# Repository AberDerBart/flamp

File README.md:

**Disclaimer:** This has been developed as a personal project and the current state was good enough for me to build it but is problably not well suited to recreate.
There are also changes planned (especially to the PCB and electronics).
Please contact me or open an issue if you have any problems or questions on this project, I am happy to help (but not very motivated to do documentation work upfront).

If you want or need another license for some reason (especially for commercial use), feel free to contact me.

# Flamp

These are the design files for my flower lamp (short "Flamp"), A dimmable ceiling lamp inspired by a flower blossom with servo-actuated petals to open up or close down.

## Getting started

Check out this repository using the [`--recurse-submodules`](https://git-scm.com/docs/git-clone#Documentation/git-clone.txt---recurse-submodulespathspec) flag.

For the mechanical design, open `lamp.scad` in OpenSCAD. This gives an overview how the lamp is assembled.

For the PCB design, open [pcb/pcb.kicad_pro](pcb/pcb.kicad_pro) in KiCad.

## Necessary parts

For hardware and electronic parts, see [BOM.csv](BOM.csv).
You need to 3D print the parts from [cad/printed_parts.scad](cad/printed_parts.scad).
The design for the wooden parts can be found in [cad/wooden_parts_12mm.scad](cad/wooden_parts_12mm.scad) and [cad/wooden_parts_4mm.scad](cad/wooden_parts_4mm.scad).

1. Cut the parts with a CNC router or laser cutter from 12mm or 4mm plywood respectively
2. 3D print the [jigs](cad/jigs.scad) and use them to trace the shape of the wooden parts and saw them out.
   Then, use the jigs and a router to trim them to size and drill the holes using the jigs. Make sure to drill the holes before removing the inner parts.

## Assembly

TODO

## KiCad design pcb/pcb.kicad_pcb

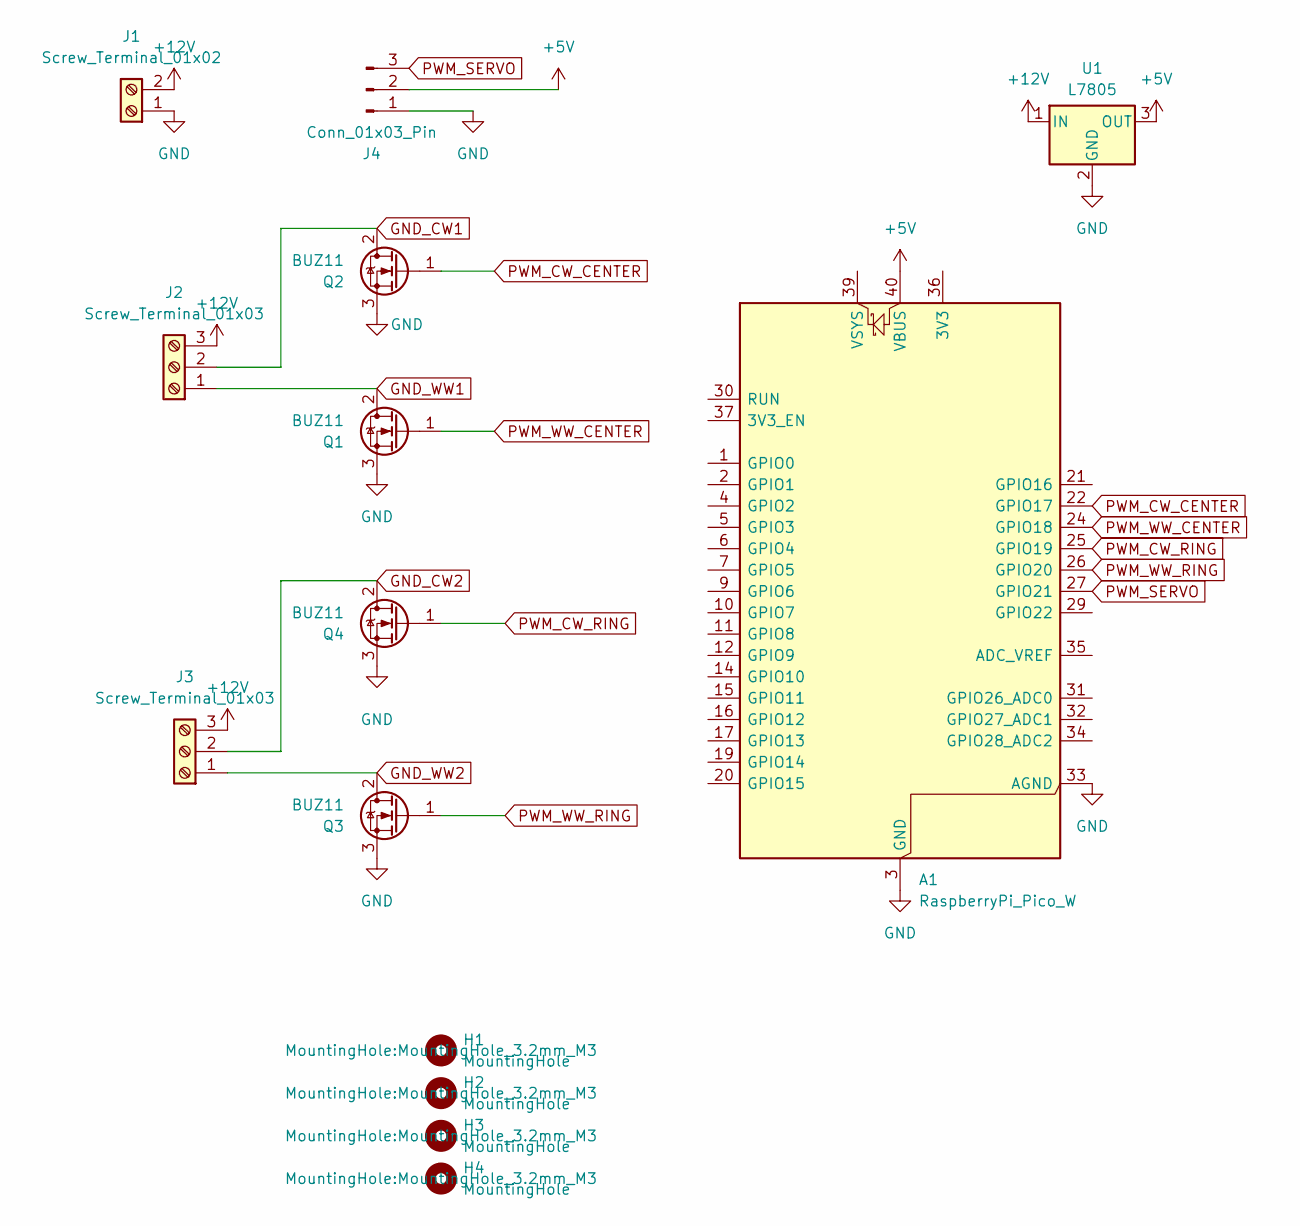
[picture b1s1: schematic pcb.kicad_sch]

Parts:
A1: RaspberryPi_Pico_W; RaspberryPi_Pico_Common_THT
H1, H2, H3, H4: MountingHole; MountingHole_3.2mm_M3
J1: Screw_Terminal_01x02; TerminalBlock_Phoenix_PT-1,5-2-3.5-H_1x02_P3.50mm_Horizontal
J2, J3: Screw_Terminal_01x03; TerminalBlock_Phoenix_PT-1,5-3-3.5-H_1x03_P3.50mm_Horizontal
J4: Conn_01x03_Pin; PinHeader_1x03_P2.54mm_Vertical
Q1, Q2, Q3, Q4: BUZ11; TO-220-3_Horizontal_TabDown
U1: L7805; TO-220-3_Horizontal_TabUp

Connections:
+5V: A1.40 (VBUS), J4.2, U1.3 (OUT)
+12V: J1.2, J2.3, J3.3, U1.1 (IN)
GND: A1.3 (GND), A1.8 (GND), A1.13 (GND), A1.18 (GND), A1.23 (GND), A1.28 (GND), A1.33 (AGND), A1.38 (GND), J1.1, J4.1, Q1.3 (S), Q2.3 (S), Q3.3 (S), Q4.3 (S), U1.2 (GND)
GND_CW1: J2.2, Q2.2 (D)
GND_CW2: J3.2, Q4.2 (D)
GND_WW1: J2.1, Q1.2 (D)
GND_WW2: J3.1, Q3.2 (D)
PWM_CW_CENTER: A1.22 (GPIO17), Q2.1 (G)
PWM_CW_RING: A1.25 (GPIO19), Q4.1 (G)
PWM_SERVO: A1.27 (GPIO21), J4.3
PWM_WW_CENTER: A1.24 (GPIO18), Q1.1 (G)
PWM_WW_RING: A1.26 (GPIO20), Q3.1 (G)

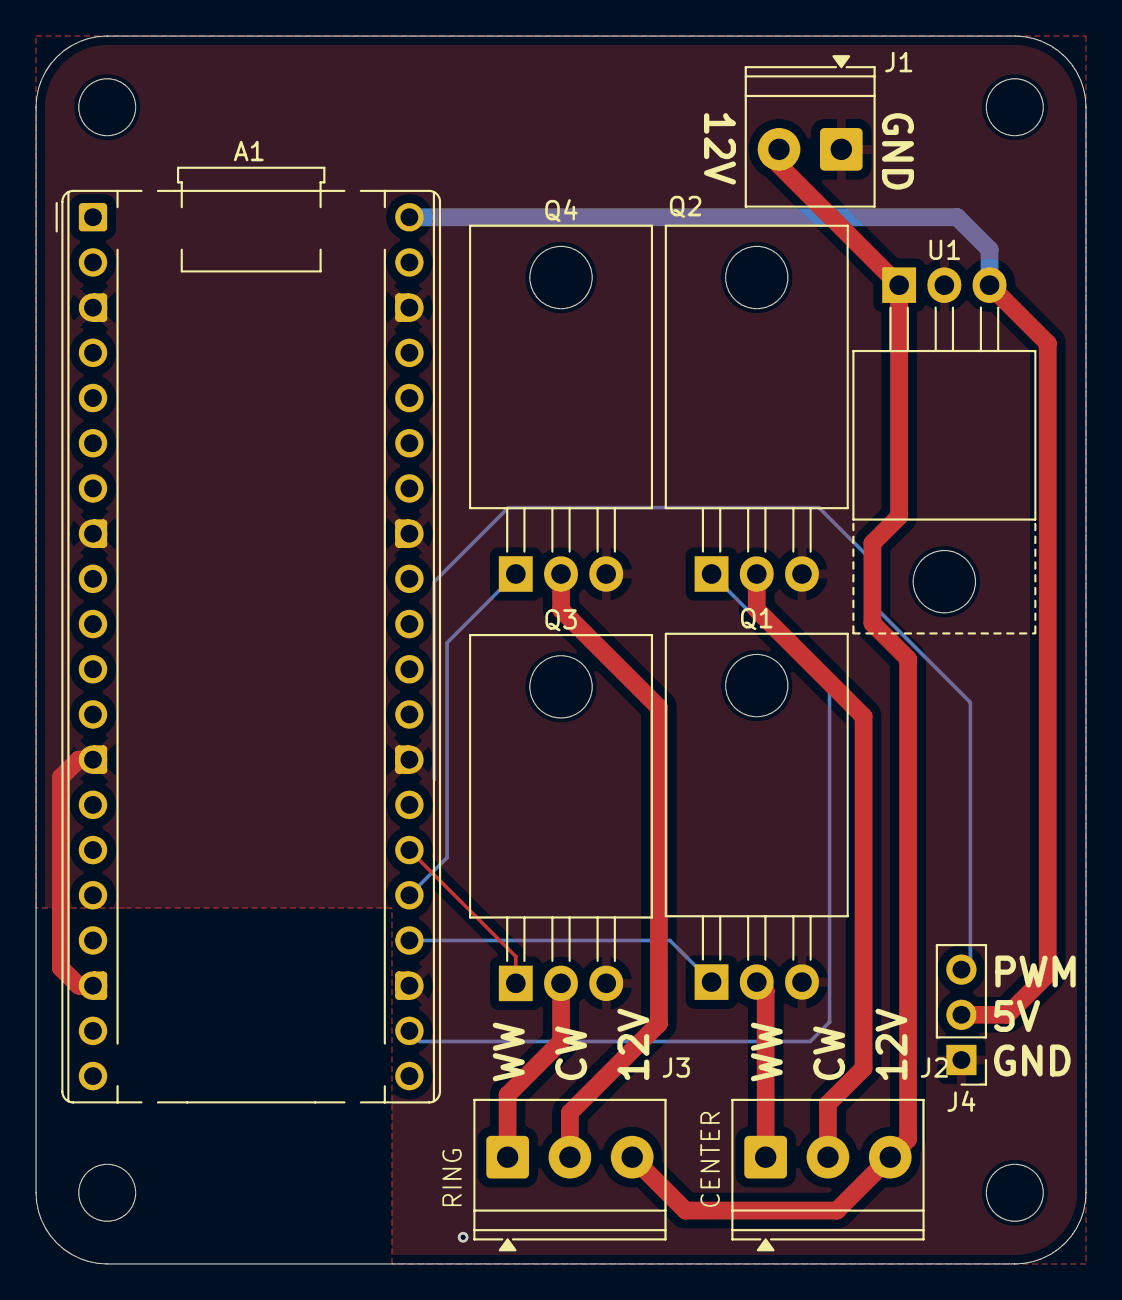
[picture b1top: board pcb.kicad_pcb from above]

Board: 2 copper layers, 59.0 x 69.0 mm, 14 parts (0 on the bottom side), 12 nets.

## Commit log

2026-01-09 add gitignore
2026-01-09 add bottom leaf links
2026-01-12 add linkages
2026-01-17 add servo and bearings
2026-01-19 restructure code
2026-01-20 model top support ring
2026-01-21 curve links
2026-01-21 fine-tune mechanism
2026-01-31 redesign top leaf arms
2026-01-31 split up files
2026-02-01 move more stuff to separate files
2026-02-06 more refinements
2026-02-11 animate top leaf tilt
2026-02-12 add top leaf tilt rail
2026-02-15 add tilt support roller
2026-02-16 adjust top leaf angles
2026-02-19 improve top leaf hinge and rai
2026-02-21 add top leaf hinge roller mounting hole
2026-02-21 improve top leaves 3d printed parts
2026-02-21 adjust top leaf linkag
2026-03-11 add control structure
2026-03-11 add pcb
2026-03-12 improve bottom leaf spacer
2026-03-13 add stopper to bottom leaf link
2026-03-14 fixup! add control structure
2026-03-17 make top leaf hinges detachable
2026-03-17 redesign top leaf roller
2026-03-17 model light fixture attachment points and extract electronics
2026-03-17 mount electronics to control_frame
2026-03-17 Revert "make top leaf hinges detachable"
    This reverts commit d38aec6823b7c8e77f104803ede591a39ca52cfc.
2026-03-20 close off top leaf tilt rail
2026-03-20 add snap-fit connector to top leaf hinge
2026-03-20 fix pcb issues
2026-03-20 fixup! add snap-fit connector to top leaf hinge
2026-03-22 make space for electronics
2026-03-22 add drill holes for light fixture
2026-03-23 improve top leaf assembly jig
2026-03-23 add glue jig
2026-03-25 finalize light fixture
2026-03-27 redesign control frame
2026-03-27 add light fixture diffusor clamps
2026-03-30 fixup! redesign control frame
2026-03-30 make top frame hinges slidable with snap-fit
2026-04-03 finalize design (for now...)
2026-04-08 add license
2026-04-12 add readme
2026-04-12 add bartscad submodule
2026-04-12 add pcb stl model
2026-04-25 replace excenters with printed material
2026-04-25 move remaining printed parts into their own files
2026-04-25 add jigs file
2026-04-25 extract parts into separate files
2026-04-25 move cad files to subfolder
2026-04-25 split up structure parts by used wood
2026-04-30 add BOM and update README
